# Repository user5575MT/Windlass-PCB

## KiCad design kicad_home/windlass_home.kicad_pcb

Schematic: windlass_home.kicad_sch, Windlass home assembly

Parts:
C92: 100nF; C_Disc_D5.0mm_W2.5mm_P5.00mm
C_3V3, C_5VHF: 100nF; C_Disc_D5.0mm_W2.5mm_P5.00mm
C_3V3B: 10uF_16V; CP_Radial_D5.0mm_P2.50mm
C_5V: 10uF_25V; CP_Radial_D5.0mm_P2.50mm
C_DEV: 10uF_25V; CP_Radial_D5.0mm_P2.50mm
C_EDGE: 220nF; C_Disc_D5.0mm_W2.5mm_P5.00mm
C_IN: 10uF_50V; CP_Radial_D6.3mm_P2.50mm
C_ISO: 10uF_16V; CP_Radial_D5.0mm_P2.50mm
C_ISO_HF: 100nF; C_Disc_D5.0mm_W2.5mm_P5.00mm
C_REED: 10uF_16V; CP_Radial_D5.0mm_P2.50mm
C_TIME: 2.2uF; C_Rect_L13.0mm_W6.0mm_P10.00mm_FKS3_FKP3_MKS4
C_U12, C_U15, C_U16, C_U17: 100nF; C_Disc_D5.0mm_W2.5mm_P5.00mm
C_URX: 100nF; C_Disc_D5.0mm_W2.5mm_P5.00mm
C_UTX: 100nF; C_Disc_D5.0mm_W2.5mm_P5.00mm
D20, D21, D80: BAT46; D_DO-35_SOD27_P5.08mm_Vertical_CathodeUp
D30, D40: 1N4148; D_DO-41_SOD81_P5.08mm_Vertical_CathodeUp
D60, D70: 1N5819; D_DO-41_SOD81_P5.08mm_Vertical_CathodeUp
D_DEV: 1N5817; D_DO-41_SOD81_P5.08mm_Vertical_CathodeUp
D_G: GREEN; LED_D5.0mm
D_R: RED; LED_D5.0mm
D_TVS_COIL: P6KE18A; D_DO-41_SOD81_P5.08mm_Vertical_CathodeUp
D_TVS_MCU: P6KE18A; D_DO-41_SOD81_P5.08mm_Vertical_CathodeUp
D_Z_COIL: BZX55C12; D_DO-35_SOD27_P5.08mm_Vertical_CathodeUp
D_Z_MCU: BZX55C12; D_DO-35_SOD27_P5.08mm_Vertical_CathodeUp
F_COIL: 70-007-33/0.4A; Fuseholder_Cylinder-5x20mm_Schurter_0031_8201_Horizontal_Op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
F_MCU: 0217002.HXP; Fuseholder_Cylinder-5x20mm_Schurter_0031_8201_Horizontal_Op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
J1: DevKitC_J1; PinSocket_1x22_P2.54mm_Vertical
J3: DevKitC_J3; PinSocket_1x22_P2.54mm_Vertical
JP1: 1x02_open; PinHeader_1x02_P2.54mm_Vertical
JP_REED: 1x03; PinHeader_1x03_P2.54mm_Vertical
J_CONTACT: KF350-3.5-4P; KF350-3.5-1x04
J_NMEA: B5B-XH-A; JST_XH_B5B-XH-A_1x05_P2.50mm_Vertical
J_PERM: KF350-3.5-4P; KF350-3.5-1x04
J_PWR: KF350-3.5-2P; KF350-3.5-1x02
J_REED: B4B-XH-A; JST_XH_B4B-XH-A_1x04_P2.50mm_Vertical
J_SENSE: B5B-XH-A; JST_XH_B5B-XH-A_1x05_P2.50mm_Vertical
K_DN: 40.31.7.012.0000; Relay_SPDT_Finder_40.31
K_UP: 40.31.7.012.0000; Relay_SPDT_Finder_40.31
Q_CL_DN: BC547B; TO-92_Inline
Q_CL_UP: BC547B; TO-92_Inline
Q_COIL: IRF9540NPBF; TO-220-3_Vertical
Q_DIS: BC547B; TO-92_Inline
Q_DN: IRLZ44NPBF; TO-220-3_Vertical
Q_INV: BC547B; TO-92_Inline
Q_MCU: IRF9540NPBF; TO-220-3_Vertical
Q_REED: BC557B; TO-92_Inline
Q_SERIES: IRLZ44NPBF; TO-220-3_Vertical
Q_UP: IRLZ44NPBF; TO-220-3_Vertical
R13, R14, R61, R71, R80, R81, R90: 100k; R_Axial_DIN0207_L6.3mm_D2.5mm_P2.54mm_Vertical
R20, R31, R41, R91: 10k; R_Axial_DIN0207_L6.3mm_D2.5mm_P2.54mm_Vertical
R22, R30, R40: 4.7k; R_Axial_DIN0207_L6.3mm_D2.5mm_P2.54mm_Vertical
R23: 47k; R_Axial_DIN0207_L6.3mm_D2.5mm_P2.54mm_Vertical
R24: 51; R_Axial_DIN0414_L11.9mm_D4.5mm_P15.24mm_Horizontal
R50, R60, R70: 470; R_Axial_DIN0207_L6.3mm_D2.5mm_P2.54mm_Vertical
R82: 1k; R_Axial_DIN0207_L6.3mm_D2.5mm_P2.54mm_Vertical
R94: 120; R_Axial_DIN0414_L11.9mm_D4.5mm_P15.24mm_Horizontal
R_BASE: 1k; R_Axial_DIN0207_L6.3mm_D2.5mm_P2.54mm_Vertical
R_CL_DN: 4.7k; R_Axial_DIN0207_L6.3mm_D2.5mm_P2.54mm_Vertical
R_CL_UP: 4.7k; R_Axial_DIN0207_L6.3mm_D2.5mm_P2.54mm_Vertical
R_COIL_G: 100k; R_Axial_DIN0207_L6.3mm_D2.5mm_P2.54mm_Vertical
R_DATA: 10k; R_Axial_DIN0207_L6.3mm_D2.5mm_P2.54mm_Vertical
R_EDGE: 330; R_Axial_DIN0207_L6.3mm_D2.5mm_P2.54mm_Vertical
R_EDGE_PU: 10k; R_Axial_DIN0207_L6.3mm_D2.5mm_P2.54mm_Vertical
R_G: 680; R_Axial_DIN0207_L6.3mm_D2.5mm_P2.54mm_Vertical
R_HB: 100k; R_Axial_DIN0207_L6.3mm_D2.5mm_P2.54mm_Vertical
R_INV_B: 100k; R_Axial_DIN0207_L6.3mm_D2.5mm_P2.54mm_Vertical
R_INV_C: 10k; R_Axial_DIN0207_L6.3mm_D2.5mm_P2.54mm_Vertical
R_MCU_G: 100k; R_Axial_DIN0207_L6.3mm_D2.5mm_P2.54mm_Vertical
R_PG: 1k; R_Axial_DIN0207_L6.3mm_D2.5mm_P2.54mm_Vertical
R_PGPU: 10k; R_Axial_DIN0207_L6.3mm_D2.5mm_P2.54mm_Vertical
R_R: 680; R_Axial_DIN0207_L6.3mm_D2.5mm_P2.54mm_Vertical
R_REED_B: 47k; R_Axial_DIN0207_L6.3mm_D2.5mm_P2.54mm_Vertical
R_REED_C: 1k; R_Axial_DIN0207_L6.3mm_D2.5mm_P2.54mm_Vertical
R_RX: 270; R_Axial_DIN0207_L6.3mm_D2.5mm_P2.54mm_Vertical
R_RXPU: 10k; R_Axial_DIN0207_L6.3mm_D2.5mm_P2.54mm_Vertical
R_SER_PD: 100k; R_Axial_DIN0207_L6.3mm_D2.5mm_P2.54mm_Vertical
R_TIME: 470k; R_Axial_DIN0207_L6.3mm_D2.5mm_P2.54mm_Vertical
R_TX: 270; R_Axial_DIN0207_L6.3mm_D2.5mm_P2.54mm_Vertical
R_TXPU: 10k; R_Axial_DIN0207_L6.3mm_D2.5mm_P2.54mm_Vertical
U4: MEJ2S0503SC; Murata_MEJ2SxxxxSC
U6, U7: PC817; DIP-4_W7.62mm
U9: MEJ2S0505SC; Murata_MEJ2SxxxxSC
U12: CD74HCT14E; DIP-14_W7.62mm
U15: CD74HCT125E; DIP-14_W7.62mm
U16: SN74HC00N; DIP-14_W7.62mm
U17: SN74HC08N; DIP-14_W7.62mm
U20: OKI-78SR-5/1.5-W36H-C; Converter_DCDC_Murata_OKI-78SR_Horizontal
U_CAN: MCP2562-E/P; DIP-8_W7.62mm
U_PG: PC817; DIP-4_W7.62mm
U_RD: PC817; DIP-4_W7.62mm
U_RX: 6N137; DIP-8_W7.62mm
U_TX: 6N137; DIP-8_W7.62mm

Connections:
+3V3: C_3V3.1, C_3V3B.1, C_U16.1, C_U17.1, D80.1 (K), J1.1, J1.2, R31.1, R41.1, R_DATA.1, R_INV_C.1, R_PGPU.1, R_RXPU.1, R_TX.1, U16.14 (VCC), U17.14 (VCC)
+5V: C_5V.1, C_5VHF.1, C_U12.1, C_U15.1, C_URX.1, D_DEV.2 (A), JP1.1 (A), R_EDGE_PU.2, R_TIME.1, U4.1 (+Vin), U12.14 (VCC), U15.10 (3OE), U15.13 (4OE), U15.14 (VCC), U20.3 (OUT), U_RX.7 (EN), U_RX.8 (VCC)
+12V_COIL: D_Z_COIL.1 (K), J_PERM.1, Q_COIL.3 (S)
+12V_MCU: C_IN.1, D_Z_MCU.1 (K), Q_MCU.3 (S), U20.1 (IN)
BLOCKED: U16.8 (3Y), U16.13 (4B)
CAN_H: J_NMEA.4, U_CAN.7 (CANH)
CAN_L: J_NMEA.2, U_CAN.6 (CANL)
CAN_RXD: U_CAN.4 (RXD), U_RX.3 (C)
CAN_TXD: R_TXPU.2, U_CAN.1 (TXD), U_TX.6 (VO)
CAN_VIN: JP1.2 (B), R90.1, R91.2, U9.1 (+Vin)
CLDN_B: Q_CL_DN.2 (B), R_CL_DN.2
CLUP_B: Q_CL_UP.2 (B), R_CL_UP.2
COIL_12: D60.1 (K), D70.1 (K), J_PERM.4, K_DN.A1, K_UP.A1, R80.1
COIL_DIV: D80.2 (A), R80.2, R81.1, R82.1
DEV_5V: C_DEV.1, D_DEV.1 (K), J1.21
DISCH: R_BASE.1, U12.4 (2Y)
DISCH_B: Q_DIS.2 (B), R_BASE.2
DN_COM: J_CONTACT.3, K_DN.11
DN_DRV: R70.1, R_CL_UP.1, U15.6 (2Y)
DN_FIELD: J_SENSE.4, R40.1
DN_GATE: Q_CL_DN.1 (C), Q_DN.1 (G), R70.2, R71.1
DN_LED: D40.1 (K), R40.2, U7.1
DN_LOW: D70.2 (A), K_DN.A2, Q_DN.2 (D)
DN_NO: J_CONTACT.4, K_DN.14
DN_RET: D40.2 (A), J_SENSE.5, U7.2
DRY_A: JP_REED.3 (B), J_REED.3, R22.2
EDGE: C_EDGE.2, R_EDGE_PU.1, U12.3 (2A)
EDGE_R: C_EDGE.1, R_EDGE.2
GND: C_3V3.2, C_3V3B.2, C_5V.2, C_5VHF.2, C_DEV.2, C_IN.2, C_TIME.2, C_U12.2, C_U15.2, C_U16.2, C_U17.2, C_URX.2, D_G.1 (K), D_R.1 (K), D_TVS_COIL.2 (A), D_TVS_MCU.2 (A), J1.22, J3.1, J3.21, J3.22, J_PWR.2, Q_CL_DN.3 (E), Q_CL_UP.3 (E), Q_DIS.3 (E), Q_INV.3 (E), Q_SERIES.3 (S), R13.2, R14.2, R61.2, R71.2, R81.2, R90.2, R_COIL_G.2, R_HB.2, R_MCU_G.2, R_SER_PD.2, U4.2 (-Vin), U6.3, U7.3, U9.2 (-Vin), U12.7 (GND), U12.9 (4A), U12.11 (5A), U12.13 (6A), U15.1 (1OE), U15.4 (2OE), U15.7 (GND), U15.9 (3A), U15.12 (4A), U16.7 (GND), U17.4 (2A), U17.5 (2B), U17.7 (GND), U17.9 (3A), U17.10 (3B), U17.12 (4A), U17.13 (4B), U20.2 (GND), U_PG.3, U_RD.3, U_RX.5 (GND)
GND_CAN: C92.2, C_ISO.2, C_ISO_HF.2, C_UTX.2, J_NMEA.1, R94.2, U9.5 (-Vout), U_CAN.2 (VSS), U_CAN.8 (STBY), U_TX.5 (GND)
GPIO1: J3.4, R_HB.1, U12.1 (1A)
GPIO4: J1.4, U_TX.3 (C)
GPIO5: J1.5, R_RXPU.2, U_RX.6 (VO)
GPIO6: J1.6, U17.3 (1Y)
GPIO7: J1.7, R31.2, U6.4
GPIO8: J1.12, R41.2, U7.4
GPIO9: J1.15, R13.1, U15.2 (1A)
GPIO10: J1.16, R14.1, U15.5 (2A)
GPIO14: J1.20, R82.2
GPIO15: J1.8, R_R.1
GPIO16: J1.9, R_G.1
GPIO18: J1.11, R91.1
HB_N: R_EDGE.1, U12.2 (1Y)
INV_B: Q_INV.2 (B), R_INV_B.2
ISO_5V: C_ISO.1, C_ISO_HF.1, C_UTX.1, R94.1, R_RX.1, R_TXPU.1, U9.7 (+Vout), U_CAN.3 (VDD), U_TX.7 (EN), U_TX.8 (VCC)
LED_G: D_G.2 (A), R_G.2
LED_R: D_R.2 (A), R_R.2
LOFRANS_NODE: D20.2 (A), D21.1 (K), JP_REED.1 (A), R20.2
NMEA_SHIELD: C92.1, J_NMEA.3
NOT_DATA: Q_INV.1 (C), R_INV_C.2, U16.5 (2B)
NQ: U16.10 (3B), U16.11 (4Y), U17.2 (1B)
NR: U16.6 (2Y), U16.12 (4A)
PG: U16.3 (1Y), U16.4 (2A), U16.9 (3A)
PG_A: R_PG.2, U_PG.1
PG_N: R_PGPU.2, U16.1 (1A), U16.2 (1B), U_PG.4
QCOIL_G: D_Z_COIL.2 (A), Q_COIL.1 (G), R_COIL_G.1
QMCU_G: D_Z_MCU.2 (A), Q_MCU.1 (G), R_MCU_G.1
RD_A: R_REED_C.2, U_RD.1
REED_3V3: C_REED.1, D20.1 (K), Q_REED.3 (E), R22.1, R24.1, R_PG.1, U4.7 (+Vout)
REED_B: Q_REED.2 (B), R_REED_B.2
REED_C: Q_REED.1 (C), R_REED_C.1
REED_DATA: R_DATA.2, R_INV_B.1, U17.1 (1A), U_RD.4
REED_ISO: JP_REED.2 (C), R23.1, R_REED_B.1
REED_RET: C_REED.2, D21.2 (A), J_REED.2, J_REED.4, R23.2, R24.2, U4.5 (-Vout), U_PG.2, U_RD.2
REED_SIG: J_REED.1, R20.1
RX_A: R_RX.2, U_RX.2 (A)
SERIES_DRAIN: Q_DN.3 (S), Q_SERIES.2 (D), Q_UP.3 (S)
SW_LINK: J_PERM.2, J_PERM.3
TIME: C_TIME.1, Q_DIS.1 (C), R_TIME.2, U12.5 (3A)
TX_A: R_TX.2, U_TX.2 (A)
UP_COM: J_CONTACT.1, K_UP.11
UP_DRV: R60.1, R_CL_DN.1, U15.3 (1Y)
UP_FIELD: J_SENSE.1, R30.1
UP_GATE: Q_CL_UP.1 (C), Q_UP.1 (G), R60.2, R61.1
UP_LED: D30.1 (K), R30.2, U6.1
UP_LOW: D60.2 (A), K_UP.A2, Q_UP.2 (D)
UP_NO: J_CONTACT.2, K_UP.14
UP_RET: D30.2 (A), J_SENSE.2, U6.2
VIN_12: F_COIL.1, F_MCU.1, J_PWR.1
VIN_COIL: D_TVS_COIL.1 (K), F_COIL.2, Q_COIL.2 (D)
VIN_MCU: D_TVS_MCU.1 (K), F_MCU.2, Q_MCU.2 (D)
WDI_GATE: Q_SERIES.1 (G), R50.2, R_SER_PD.1
WDI_Q: R50.1, U12.6 (3Y)

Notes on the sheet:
WINDLASS HOME ASSEMBLY. Through-hole and plug-in modules only. 100 x 100 mm, two layers.\nThe v2 board and the firmware are unchanged. GPIO numbers are the existing map.\nWatchdog is one CD74HCT14E. A 74HCT123 is not used: once CEXT is above 10 nF the retrigger\ngap is about 0.42 of the pulse, so a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

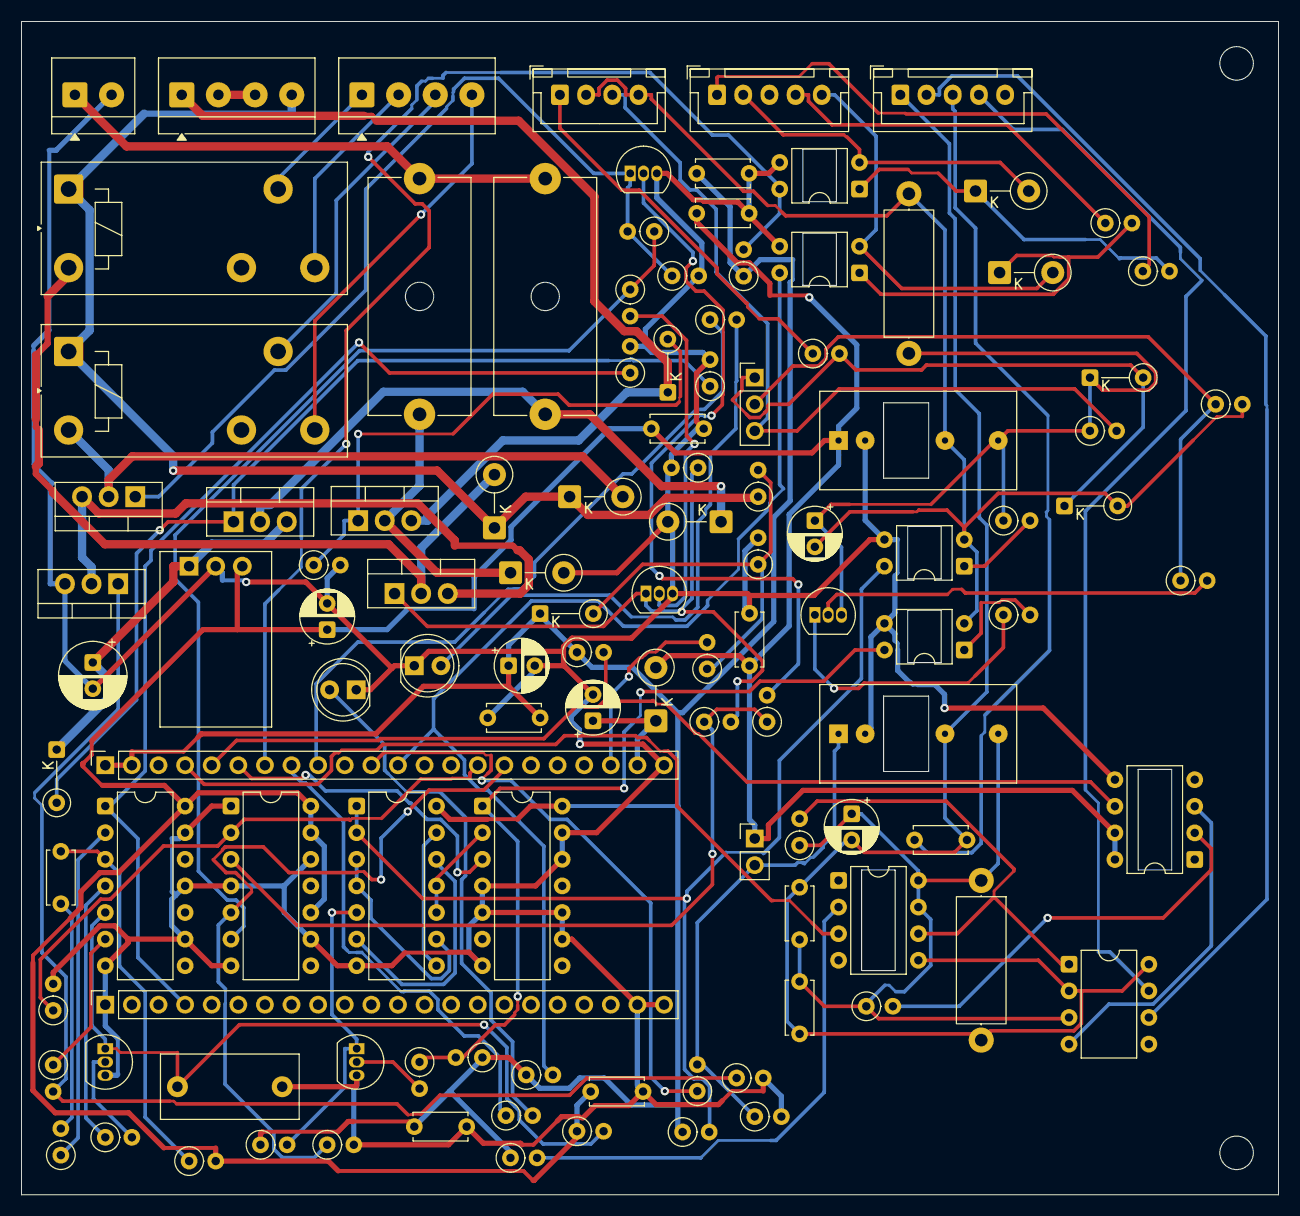
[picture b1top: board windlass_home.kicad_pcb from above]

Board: 2 copper layers, 120.0 x 112.0 mm, 116 parts (0 on the bottom side), 83 nets.

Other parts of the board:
H2, H4: M3; MountingHole_3.2mm_M3

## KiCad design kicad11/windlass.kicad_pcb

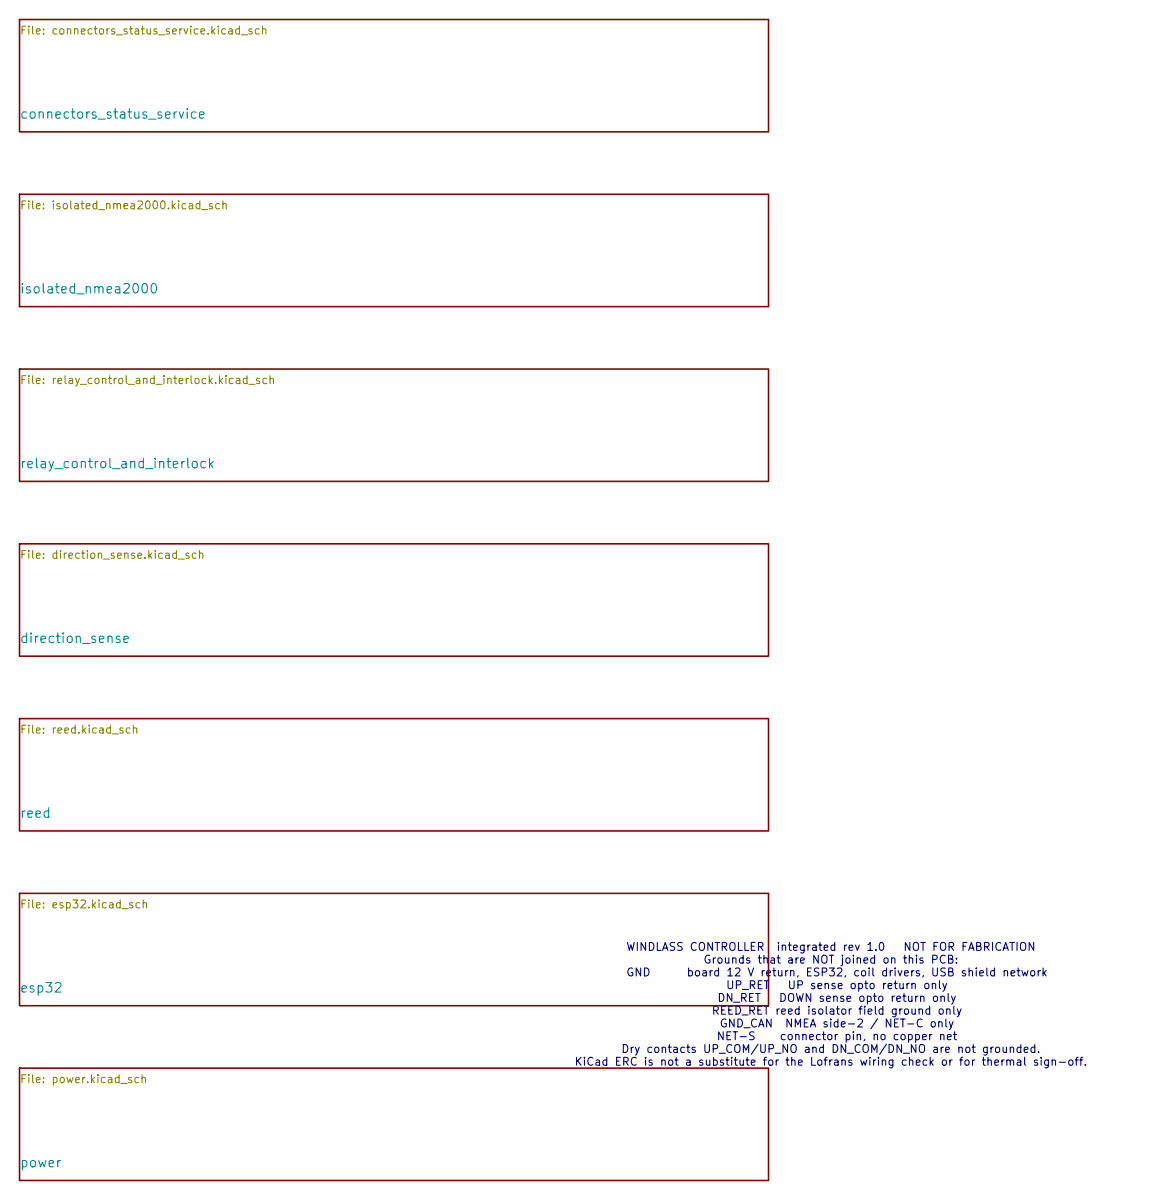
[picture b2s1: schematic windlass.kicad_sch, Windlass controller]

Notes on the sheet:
WINDLASS CONTROLLER integrated rev 1.0 NOT FOR FABRICATION Grounds that are NOT joined on this PCB: GND board 12 V return, ESP32, coil drivers, USB shield network UP_RET UP sense opto return only DN_RET DOWN sense opto return only REED_RET reed isolator field ground only GND_CAN NMEA side-2 / NET-C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

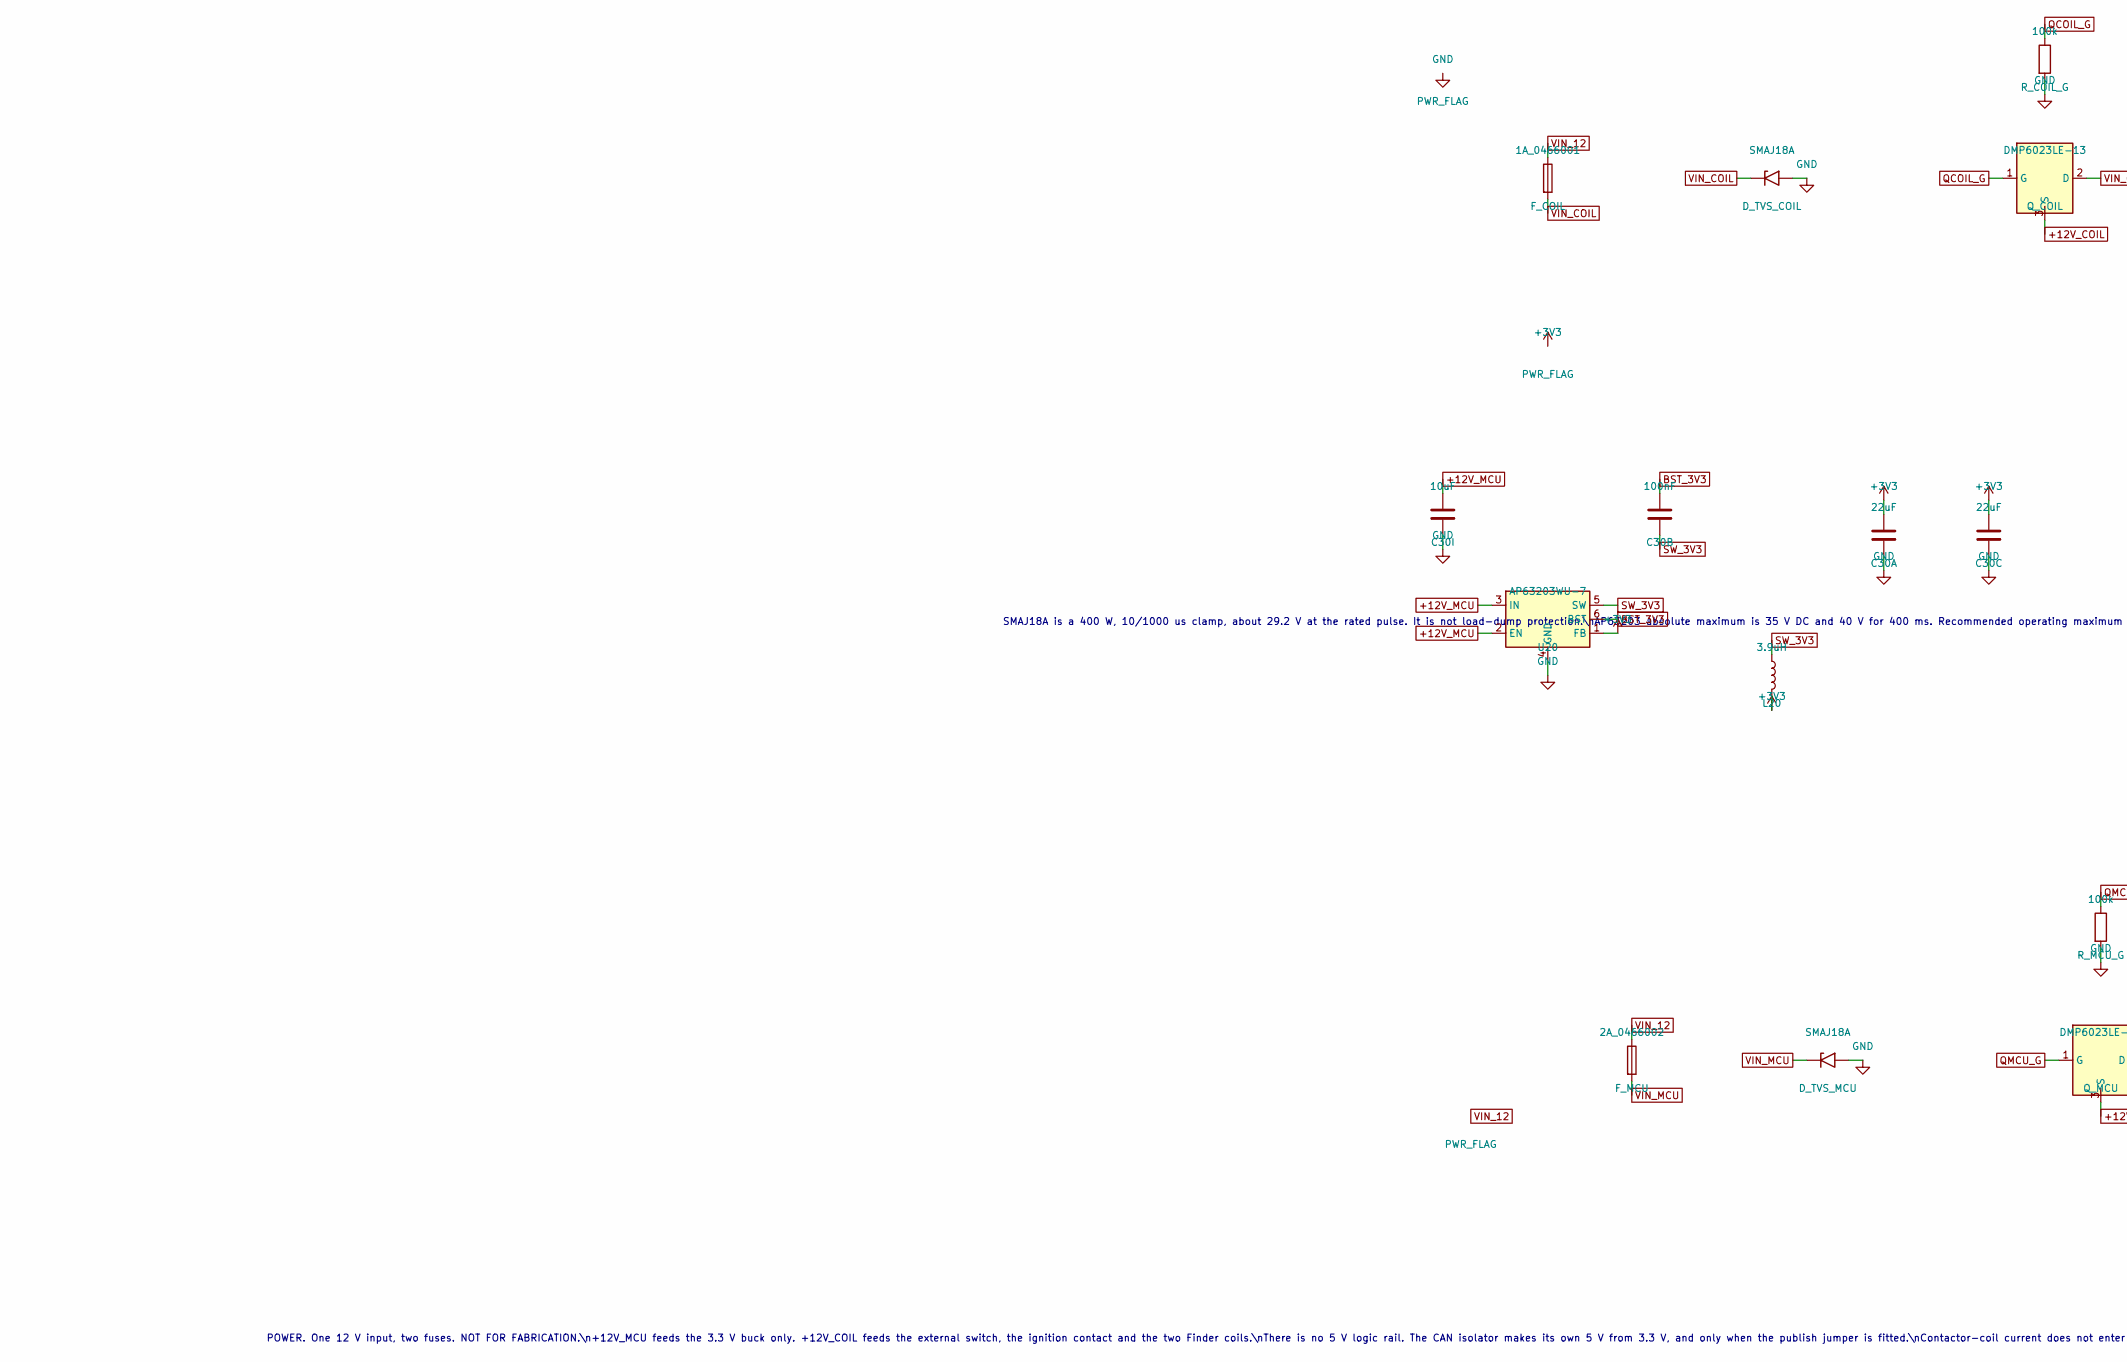
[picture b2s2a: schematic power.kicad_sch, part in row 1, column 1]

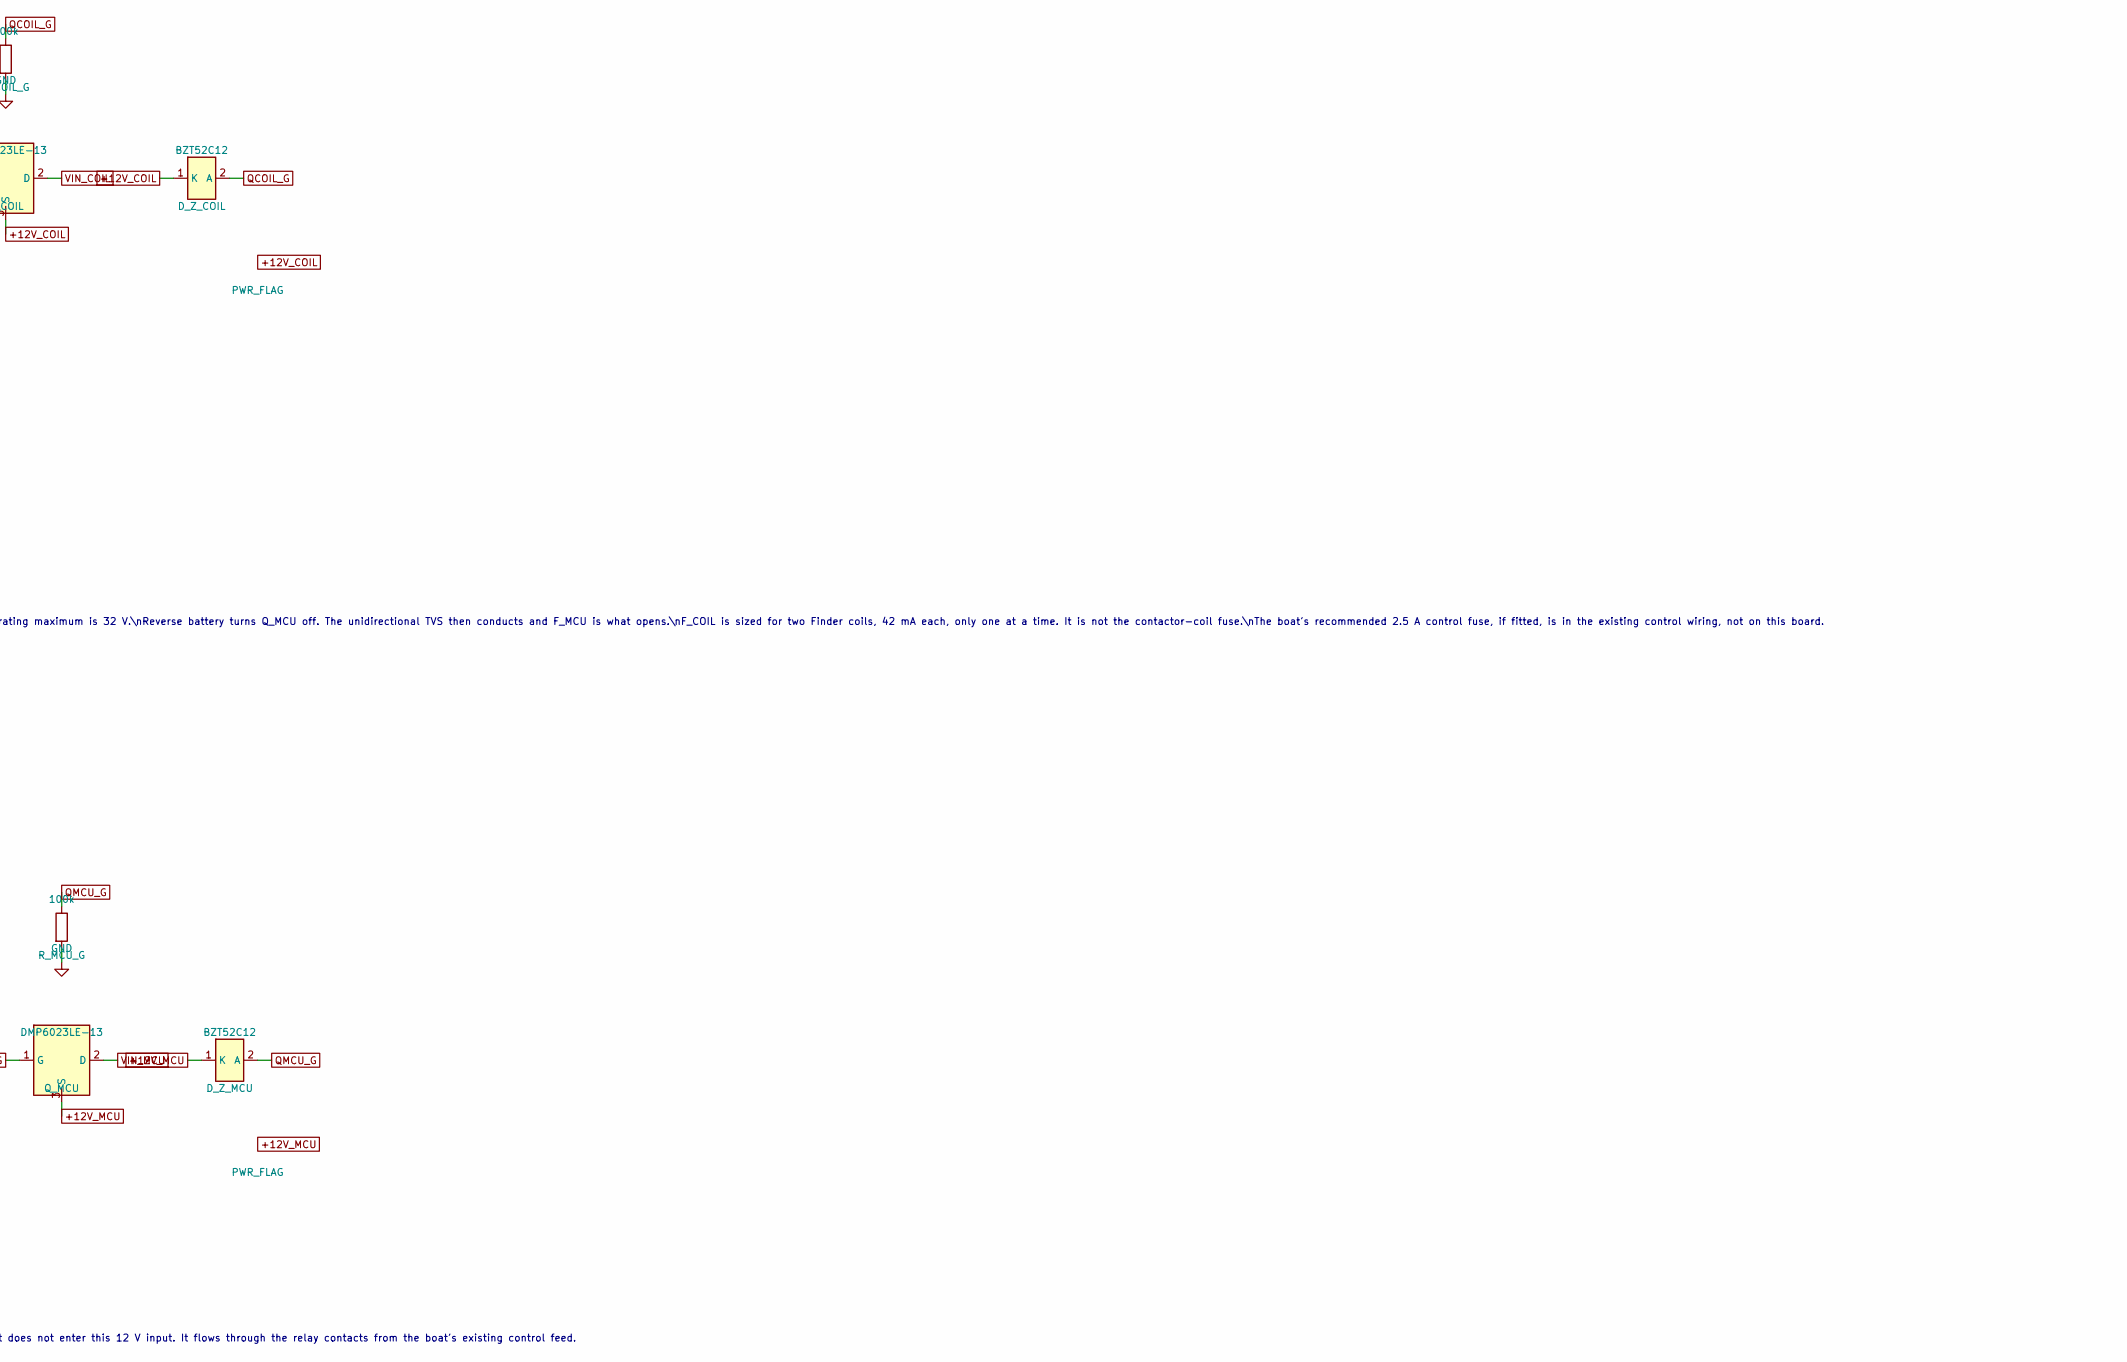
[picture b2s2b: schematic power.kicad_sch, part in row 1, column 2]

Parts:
C30A, C30C: 22uF; C_0805_2012Metric
C30B: 100nF; C_0402_1005Metric
C30I: 10uF; C_0805_2012Metric
D_TVS_COIL: SMAJ18A; D_SMA
D_TVS_MCU: SMAJ18A; D_SMA
D_Z_COIL: BZT52C12; D_SOD-123
D_Z_MCU: BZT52C12; D_SOD-123
F_COIL: 1A_0466001; Fuse_1206_3216Metric
F_MCU: 2A_0466002; Fuse_1206_3216Metric
L20: 3.9uH; L_Bourns-SRN4018
Q_COIL: DMP6023LE-13; SOT-223-3_TabPin2
Q_MCU: DMP6023LE-13; SOT-223-3_TabPin2
R_COIL_G: 100k; R_0402_1005Metric
R_MCU_G: 100k; R_0402_1005Metric
U20: AP63203WU-7; TSOT-23-6

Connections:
+3V3: C30A.1, C30C.1, L20.2, U20.1 (FB); also elsewhere on the board
+12V_COIL: D_Z_COIL.1 (K), Q_COIL.3 (S); also elsewhere on the board
+12V_MCU: C30I.1, D_Z_MCU.1 (K), Q_MCU.3 (S), U20.2 (EN), U20.3 (IN)
BST_3V3: C30B.1, U20.6 (BST)
GND: C30A.2, C30C.2, C30I.2, D_TVS_COIL.2 (A2), D_TVS_MCU.2 (A2), R_COIL_G.2, R_MCU_G.2, U20.4 (GND); also elsewhere on the board
QCOIL_G: D_Z_COIL.2 (A), Q_COIL.1 (G), R_COIL_G.1
QMCU_G: D_Z_MCU.2 (A), Q_MCU.1 (G), R_MCU_G.1
SW_3V3: C30B.2, L20.1, U20.5 (SW)
VIN_12: F_COIL.1, F_MCU.1; also elsewhere on the board
VIN_COIL: D_TVS_COIL.1 (A1), F_COIL.2, Q_COIL.2 (D)
VIN_MCU: D_TVS_MCU.1 (A1), F_MCU.2, Q_MCU.2 (D)

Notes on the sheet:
POWER. One 12 V input, two fuses. NOT FOR FABRICATION.\n+12V_MCU feeds the 3.3 V buck only. +12V_COIL feeds the external switch, the ignition contact and the two Finder coils.\nThere is no 5 V logic rail. The CAN isolator makes its own 5 V from 3.3 V, and only when the publish jumper is fitted.\nCo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
SMAJ18A is a 400 W, 10/1000 us clamp, about 29.2 V at the rated pulse. It is not load-dump protection.\nAP63203 absolute maximum is 35 V DC and 40 V for 400 ms. Recommended operating maximum is 32 V.\nReverse battery turns Q_MCU off. The unidirectional TVS then conducts and F_MCU is what opens.\nF_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

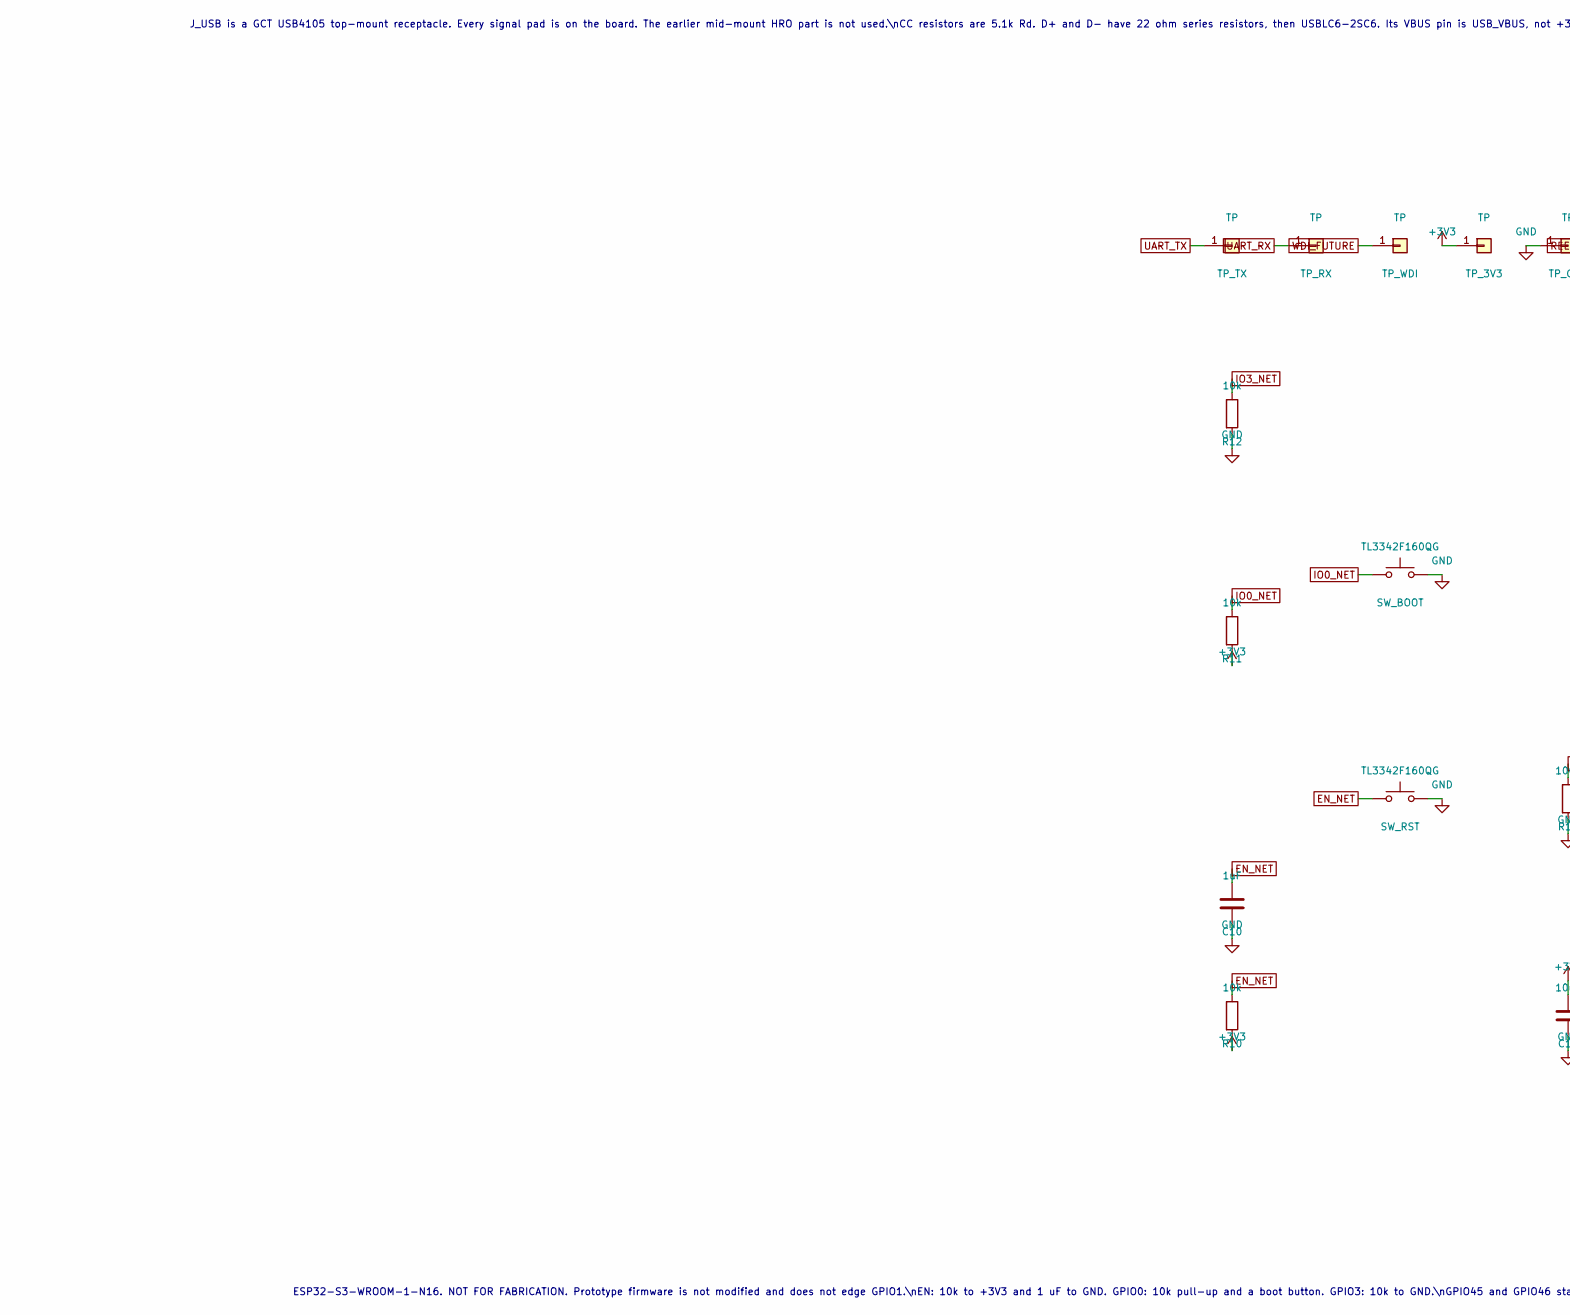
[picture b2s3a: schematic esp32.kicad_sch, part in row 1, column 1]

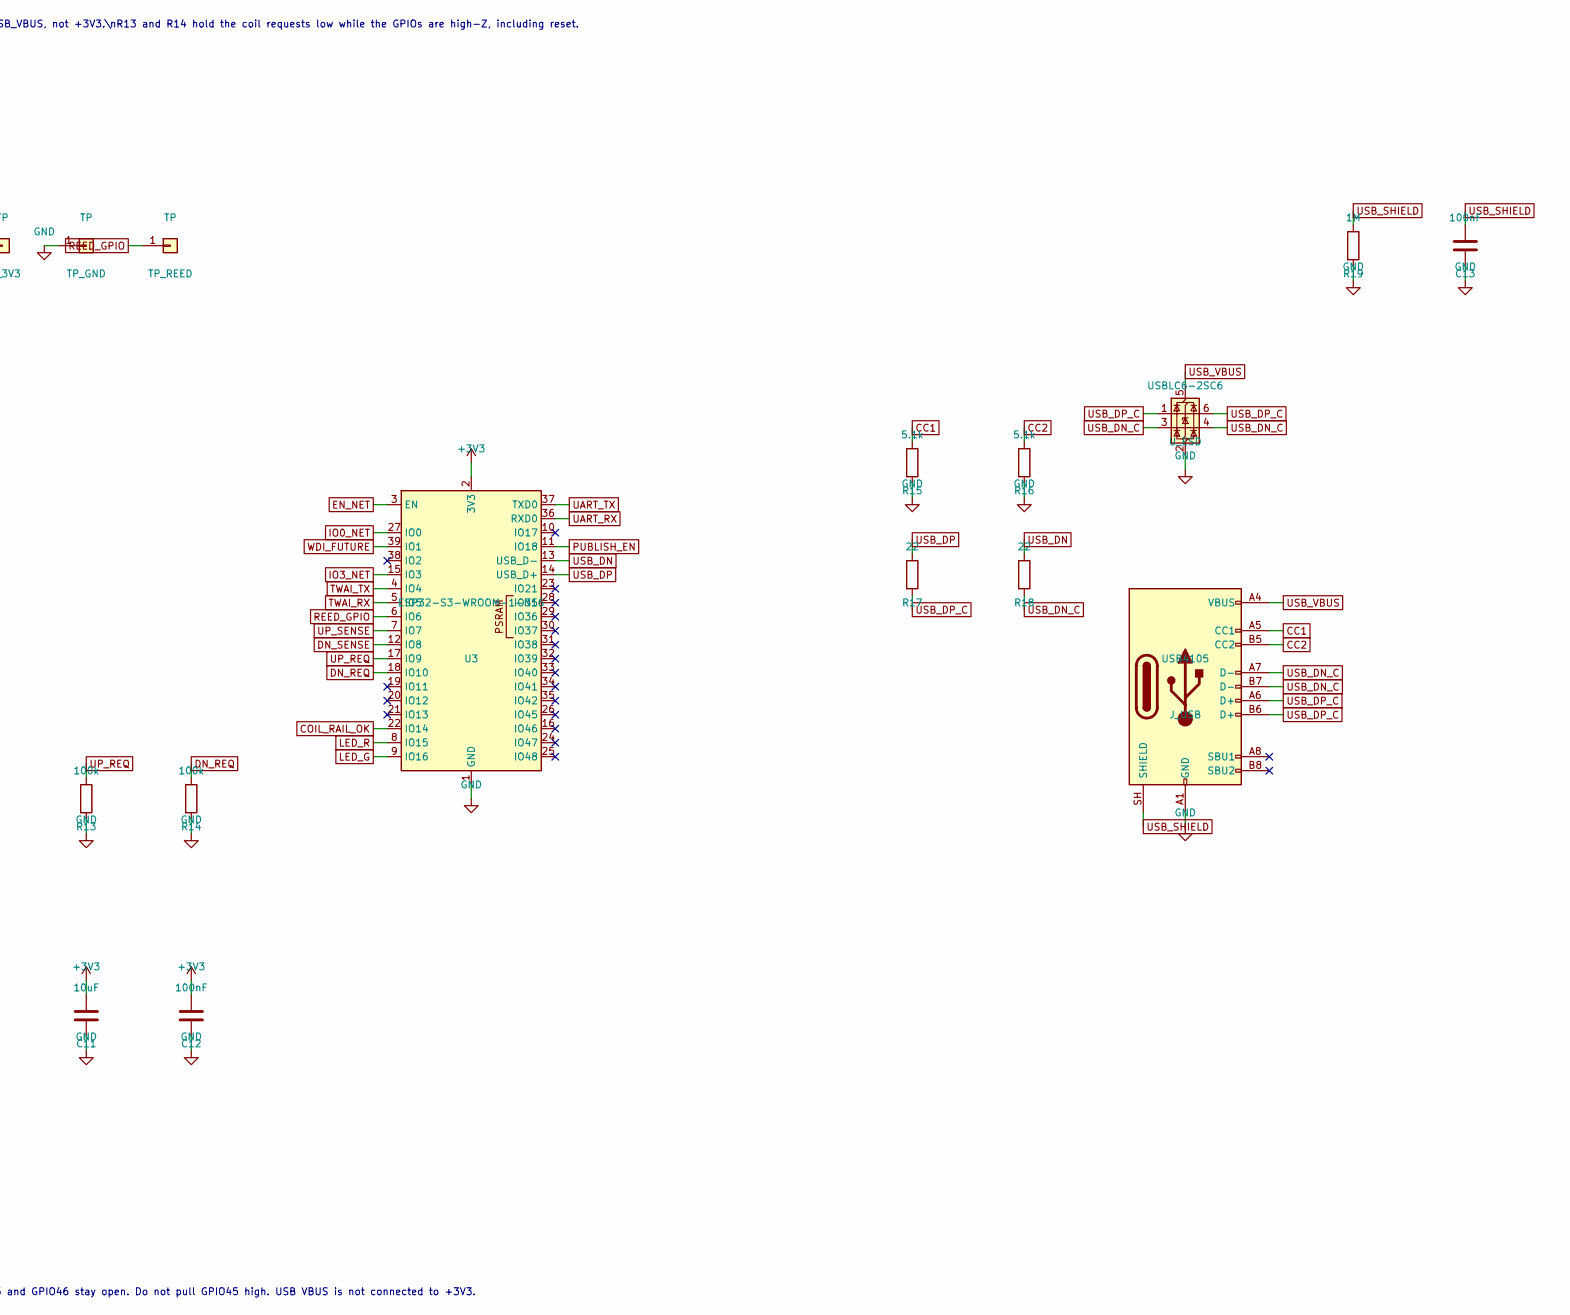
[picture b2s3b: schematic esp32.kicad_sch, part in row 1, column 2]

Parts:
C10: 1uF; C_0805_2012Metric
C11: 10uF; C_0805_2012Metric
C12, C13: 100nF; C_0402_1005Metric
J_USB: USB4105; USB_C_Receptacle_GCT_USB4105-xx-A_16P_TopMnt_Horizontal
R10, R11, R12: 10k; R_0402_1005Metric
R13, R14: 100k; R_0402_1005Metric
R15, R16: 5.1k; R_0402_1005Metric
R17, R18: 22; R_0402_1005Metric
R19: 1M; R_0402_1005Metric
SW_BOOT: TL3342F160QG; SW_SPST_TL3342
SW_RST: TL3342F160QG; SW_SPST_TL3342
TP_3V3: TP; TestPoint_Pad_D1.5mm
TP_GND: TP; TestPoint_Pad_D1.5mm
TP_REED: TP; TestPoint_Pad_D1.5mm
TP_RX: TP; TestPoint_Pad_D1.5mm
TP_TX: TP; TestPoint_Pad_D1.5mm
TP_WDI: TP; TestPoint_Pad_D1.5mm
U3: ESP32-S3-WROOM-1-N16; ESP32-S3-WROOM-1
U_ESD: USBLC6-2SC6; SOT-23-6

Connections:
+3V3: C11.1, C12.1, R10.2, R11.2, TP_3V3.1, U3.2 (3V3); also elsewhere on the board
CC1: J_USB.A5 (CC1), R15.1
CC2: J_USB.B5 (CC2), R16.1
COIL_RAIL_OK: U3.22 (IO14); also elsewhere on the board
DN_REQ: R14.1, U3.18 (IO10); also elsewhere on the board
DN_SENSE: U3.12 (IO8); also elsewhere on the board
EN_NET: C10.1, R10.1, SW_RST.1, U3.3 (EN)
GND: C10.2, C11.2, C12.2, C13.2, J_USB.A1 (GND), J_USB.A12 (GND), J_USB.B1 (GND), J_USB.B12 (GND), R12.2, R13.2, R14.2, R15.2, R16.2, R19.2, SW_BOOT.2, SW_RST.2, TP_GND.1, U3.1 (GND), U3.40 (GND), U3.41 (GND), U_ESD.2 (GND); also elsewhere on the board
IO0_NET: R11.1, SW_BOOT.1, U3.27 (IO0)
IO3_NET: R12.1, U3.15 (IO3)
LED_G: U3.9 (IO16); also elsewhere on the board
LED_R: U3.8 (IO15); also elsewhere on the board
PUBLISH_EN: U3.11 (IO18); also elsewhere on the board
REED_GPIO: TP_REED.1, U3.6 (IO6); also elsewhere on the board
TWAI_RX: U3.5 (IO5); also elsewhere on the board
TWAI_TX: U3.4 (IO4); also elsewhere on the board
UART_RX: TP_RX.1, U3.36 (RXD0)
UART_TX: TP_TX.1, U3.37 (TXD0)
UP_REQ: R13.1, U3.17 (IO9); also elsewhere on the board
UP_SENSE: U3.7 (IO7); also elsewhere on the board
USB_DN: R18.1, U3.13 (USB_D-)
USB_DN_C: J_USB.A7 (D-), J_USB.B7 (D-), R18.2, U_ESD.3 (I/O2), U_ESD.4 (I/O2)
USB_DP: R17.1, U3.14 (USB_D+)
USB_DP_C: J_USB.A6 (D+), J_USB.B6 (D+), R17.2, U_ESD.1 (I/O1), U_ESD.6 (I/O1)
USB_SHIELD: C13.1, J_USB.SH (SHIELD), R19.1
USB_VBUS: J_USB.A4 (VBUS), J_USB.A9 (VBUS), J_USB.B4 (VBUS), J_USB.B9 (VBUS), U_ESD.5 (VBUS)
WDI_FUTURE: TP_WDI.1, U3.39 (IO1); also elsewhere on the board

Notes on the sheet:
ESP32-S3-WROOM-1-N16. NOT FOR FABRICATION. Prototype firmware is not modified and does not edge GPIO1.\nEN: 10k to +3V3 and 1 uF to GND. GPIO0: 10k pull-up and a boot button. GPIO3: 10k to GND.\nGPIO45 and GPIO46 stay open. Do not pull GPIO45 high. USB VBUS is not connected to +3V3.
J_USB is a GCT USB4105 top-mount receptacle. Every signal pad is on the board. The earlier mid-mount HRO part is not used.\nCC resistors are 5.1k Rd. D+ and D- have 22 ohm series resistors, then USBLC6-2SC6. Its VBUS pin is USB_VBUS, not +3V3.\nR13 and R14 hold the coil requests low while the GPIOs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
